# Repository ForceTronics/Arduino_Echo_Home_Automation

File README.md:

# Arduino_Echo_Home_Automation
Voice controlled home automation with Arduino (ESP8266 and MKR1000) and the Amazon Echo. Go to the ForceTronic YouTube Channel to see the video tutorial series

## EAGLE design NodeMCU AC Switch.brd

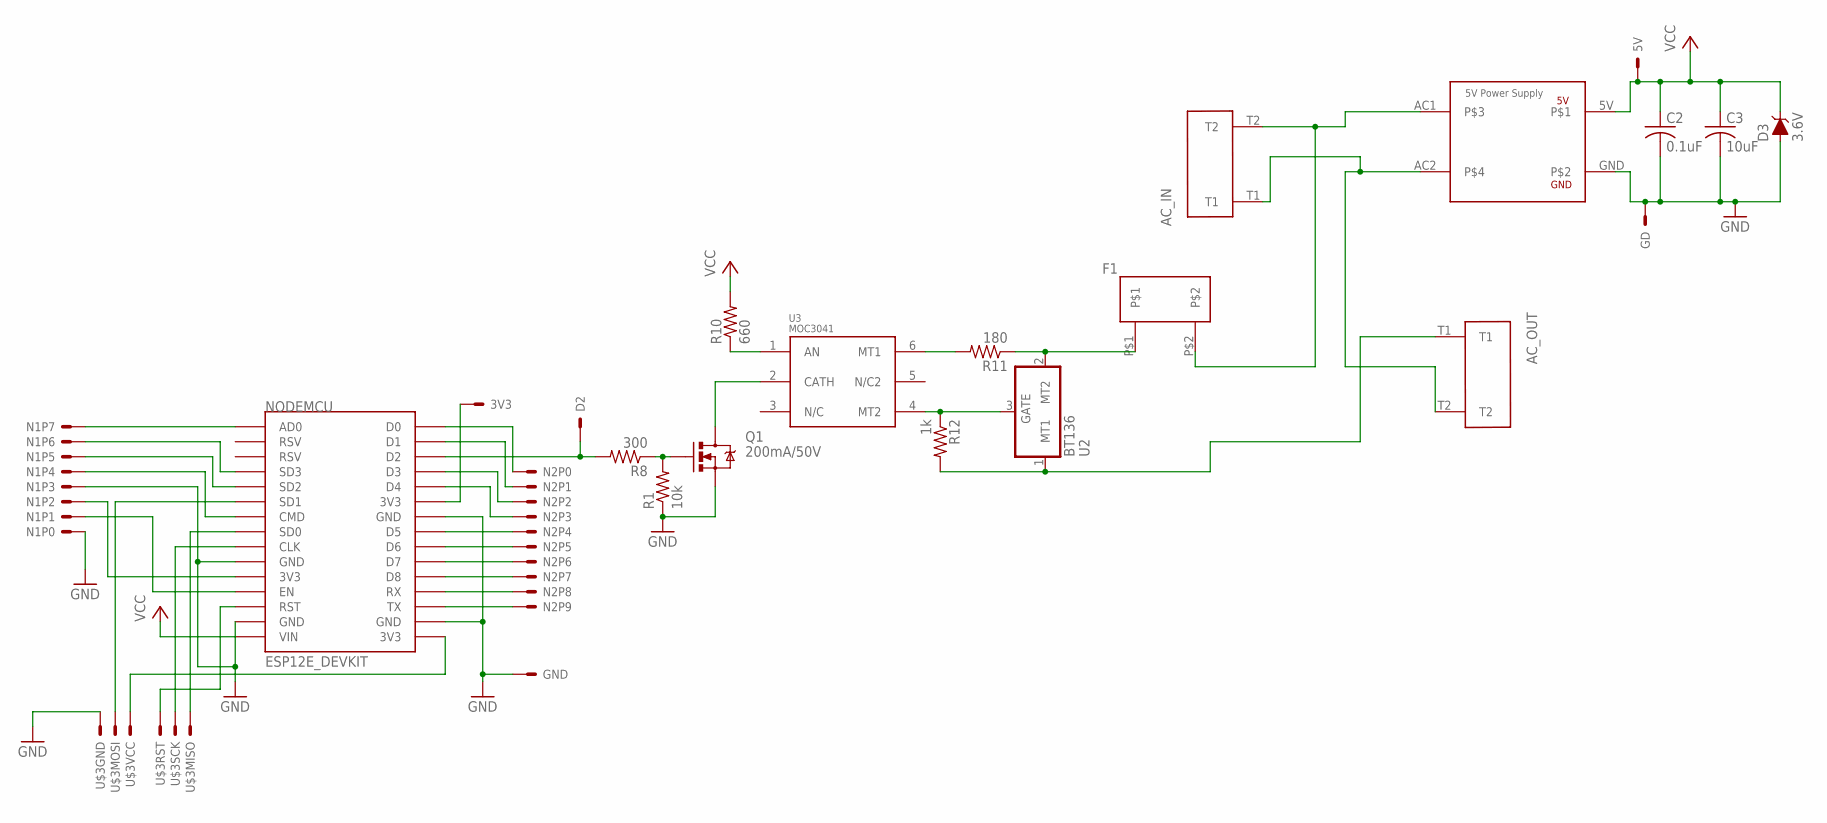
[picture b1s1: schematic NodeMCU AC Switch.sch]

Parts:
3V3, 5V: 1PINHEADER_S
AC_IN: 2PIN_SCREW_TERM
AC_OUT: 2PIN_SCREW_TERM
C2: 0.1uF; C1206
C3: 10uF; C1206
D2: 1PINHEADER_S
D3: 3.6V; SOD-323
F1: FUSE_HOLDER
GD: 1PINHEADER_S
GND: 1PINHEADER_S
N1: 8PINHEADER
N2: 10PINHEADER
NODEMCU: ESP12E_DEVKIT
Q1: 200mA/50V; SOT23-3
R1: 10k; R1206
R8: 300; R1206
R10: 660; R1206
R11: 180; R1206
R12: 1k; R1206
U2: BT136
U3: MOC3041
U$2: 5V_POWER_SUPPLY
U$3: 2X3_HEADER

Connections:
GND: C2.2, C3.2, D3.A, GD.P$1, GND.P$1, N1.P0, N1.P3, NODEMCU.GND@0 (GND), NODEMCU.GND@1 (GND), NODEMCU.GND@2 (GND), NODEMCU.GND@3 (GND), Q1.2 (S), R1.1, U$2.GND, U$3.GND
unnamed: D2.P$1, NODEMCU.D2, R8.2
unnamed: NODEMCU.SD1, U$3.MOSI
unnamed: NODEMCU.SD0, U$3.MISO
unnamed: NODEMCU.RST, U$3.RST
unnamed: NODEMCU.CLK, U$3.SCK
unnamed: NODEMCU.3V3@2 (3V3), U$3.VCC
unnamed: Q1.3 (D), U3.2 (CATH)
unnamed: F1.P$1, R11.1, U2.2 (MT2)
unnamed: N1.P7, NODEMCU.AD0
unnamed: N1.P6, NODEMCU.SD3
unnamed: N1.P5, NODEMCU.SD2
unnamed: N1.P4, NODEMCU.CMD
unnamed: N2.P0, NODEMCU.D0
unnamed: N1.P2, NODEMCU.3V3@0 (3V3)
unnamed: N1.P1, NODEMCU.EN
unnamed: N2.P1, NODEMCU.D1
unnamed: N2.P2, NODEMCU.D3
unnamed: AC_IN.T1, AC_OUT.T2, U$2.AC2
unnamed: N2.P3, NODEMCU.D4
unnamed: N2.P4, NODEMCU.D5
unnamed: N2.P5, NODEMCU.D6
unnamed: N2.P6, NODEMCU.D7
unnamed: N2.P7, NODEMCU.D8
unnamed: Q1.1 (G), R1.2, R8.1
unnamed: N2.P8, NODEMCU.RX
unnamed: N2.P9, NODEMCU.TX
unnamed: 3V3.P$1, NODEMCU.3V3@1 (3V3)
unnamed: AC_IN.T2, F1.P$2, U$2.AC1
unnamed: R10.1, U3.1 (AN)
unnamed: R11.2, U3.6 (MT1)
unnamed: R12.1, U2.3 (GATE), U3.4 (MT2)
unnamed: AC_OUT.T1, R12.2, U2.1 (MT1)
VCC: 5V.P$1, C2.1, C3.1, D3.C, NODEMCU.VIN, R10.2, U$2.5V

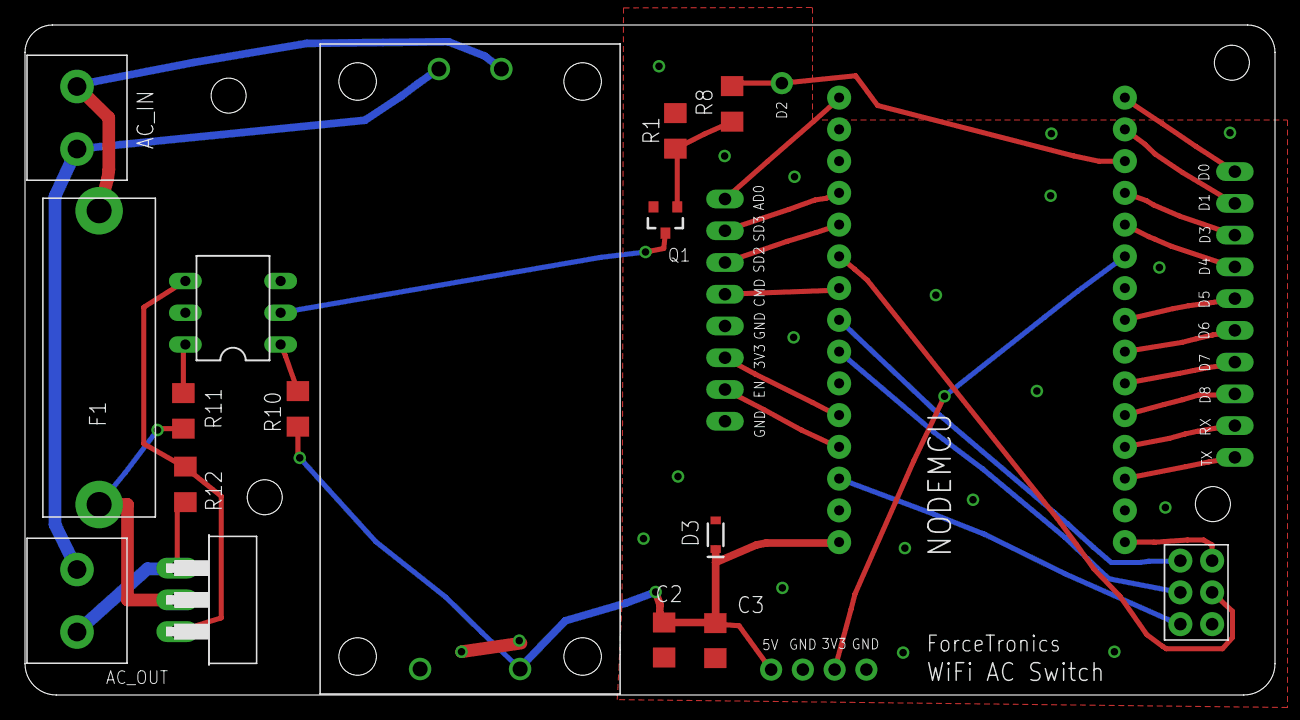
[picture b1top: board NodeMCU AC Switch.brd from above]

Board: 2 copper layers, 100.0 x 53.6 mm, 24 parts (0 on the bottom side), 34 nets.

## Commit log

2017-04-02 Create forceTronicsHomeAuto
    Code for AWS Lambda function. Done in Node js 4.3
2017-04-02 Create Alexa_Skill.json
    json structure for the ForceTronics Home Automation Alexa Skill
2017-04-07 Create Echo_Cloud_ESP8266.ino
    This sketch was created for a video series called Home Automation with the Arduino and the Amazon Echo Part 2
    That was presented on the ForceTronics YouTube Channel. This code is public domain for anybody to use or modify at your own risk
    Note that this code was leveraged from a Sparkfun example on using their cloud service Phant
2017-04-07 Create NodeMCU AC Switch.brd
    This PCB design was created for a video series called Home Automation with the Arduino and the Amazon Echo Part 2
    That was presented on the ForceTronics YouTube Channel. You can purchase this board by going to forcetronics.com This design is public domain for anybody to use or modify at your own risk
2017-05-27 Update forceTronicsHomeAuto
2017-05-30 Home Automation with the Arduino and the Amazon Echo
    This sketch measures the state of a washing machine by monitoring it's current. It then sends the data up to the phant cloud so it can be read and interpreted by an Amazon Echo. Go to the ForceTronic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
2017-05-30 Create PhantMKR1K.h
    Library file for using Sparkfun Phant cloud service
2017-05-30 Create PhantMKR1K.cpp
    Library file for using phant cloud service

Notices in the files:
parts and their libraries:
SparkFun-DiscreteSemi: Licensing: Creative Commons ShareAlike 4.0 International - https://creativecommons.org/licenses/by-sa/4.0
